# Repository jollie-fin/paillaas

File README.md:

# paillaas

## Context

I had decided in 2021 to leave my job and start a business, Kaukolab, to develop tools for better remote learning :

I have fond memories of session of lab work during my studies. Unfortunately, they are hard to do with remote learning. The only offers I saw on the market during my research were either based on simulations, with lots of simplification compared to the real world, or based on a few video of real experiments, but with almost no user input. Part of the experience of lab work is to experiment, break things, discover what is true and not simply check what you know is true is true.

My idea was to have real physical experiments users could connect to through Internet

## Lego prototype

A fun demonstration, where a user could control a pendulum hidden under my bed through a web interface.

The stack was the following :

- A pendulum in LEGO was hanged under my bed
- An EV3 brick with a flywheel was running a micro python kernel was communicating through an SSH connection.
  Its main tasks were : - receiving commands : - shorten/lenghten the pendulum - change how the the flywheel was controlled - retrieving and transmitting measurements from sensors - angle to the vertical - executing a simple kernel to control the flywheel
- An RPI was :
  - connected through ssh to the EV3
  - running a nodejs server that would exchange with EV3 and with a puppeteer instance
  - running a puppeteer instance that would transmit through WebRTC telemetry to a peer user, transmit a videofeed, and receive commands for the EV3
  - running a Discord bot that allowed remote management from my phone
- A remote server was :
  - serving an HTML page to the puppeteer instance on the RPI
  - serving an HTML page to end-users.
    The page was : - establishing a WebRTC connection with the RPI - displaying the telemetry to the user - allowing the user to define their own data to display through a DSL

This made for a weird stack, but it was reliable enough for me to make real demo of the concept I had.

I'm sadden that I wasn't able to push this prototype beyond it's MVP status. I had big projects like a Michelson interferometer totally controlled through internet

Some files were unfortunately lost, so I don't have a good showcase of it

## PCB design

A few pcb were designed during this adventure. Since it was in the middle of component crisis, I had to change quite a few the design, depending on component availabilities.

In hindsight, just buying a Duet Board would have been the best, but prices at that time were prohibitive

### Ethernet2serial

This is a simple serial converter, based on an atmega and an ENC28J60

### Motherboard

This aimed at connecting a Compute Module 4 to stepper motor drivers.

### Motherboard ITX-form-factor

This aimed at connecting a Compute Module 4 to stepper motor drivers. It also provides HDMI, DSI and CSI connections.

It also means I had to take care of high speed routing, with controlled impedance and differential pairs

It uses ITX screw holes, the idea being of using ITX cases

### USB2stepper

This was the final board. It is a 4 steppers board controlled by a RPI Pico, using TMC2208

A few interesting facts :

- TMC2208 were used at the limit of what they can handle
  - It means quite a bit of heat dissipation
  - Thermal vias were used to connect to the bottom side
  - A heatsink was bolted to the underside
  - To prevent short-circuit, no via (beside GND) could be used, forcing the design to be fully single layer under the heatsink
- The layer stackup was somewhat none conventional :
  - Top: signal
  - In1: GND
  - In2: GND/Power
  - Bottom: GND/Signal
  - The traces on the bottom layer were routed only over the ground plane part of In2

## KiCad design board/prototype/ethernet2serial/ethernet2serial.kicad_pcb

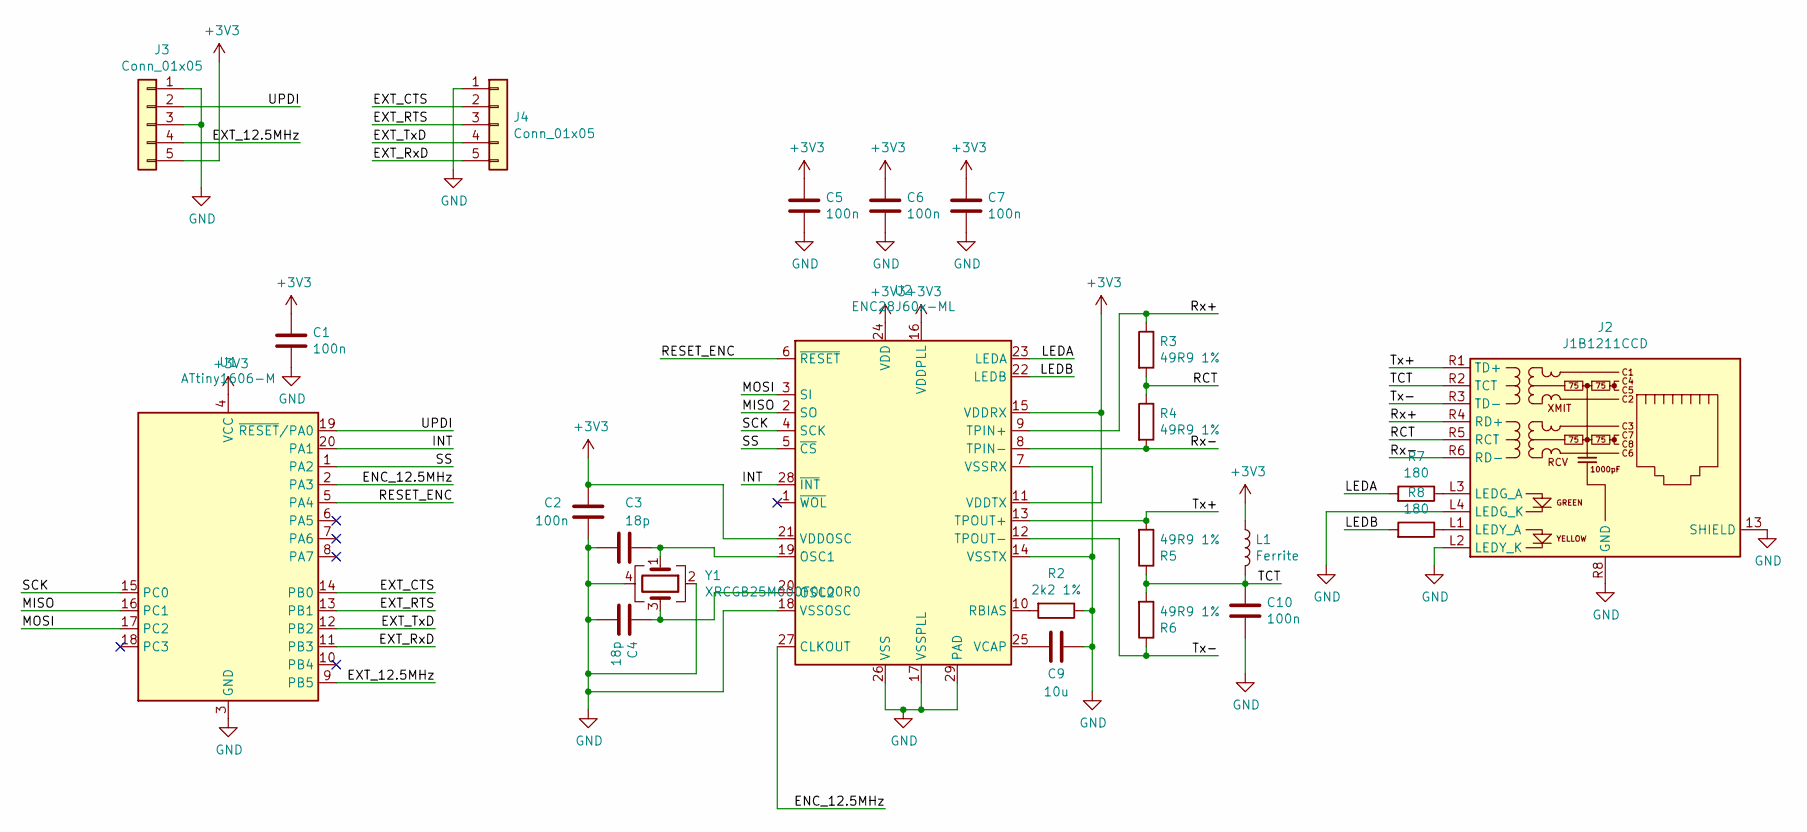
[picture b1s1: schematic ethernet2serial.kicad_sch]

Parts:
C1, C2, C5, C6, C7, C10: 100n; C_0402_1005Metric
C3, C4: 18p; C_0402_1005Metric
C9: 10u; C_0805_2012Metric
J2: J1B1211CCD; RJ45_Amphenol_RJMG1BD3B8K1ANR
J3, J4: Conn_01x05; PinHeader_1x05_P2.54mm_Vertical
L1: Ferrite; L_0402_1005Metric
R2: 2k2 1%; R_0402_1005Metric
R3, R4, R5, R6: 49R9 1%; R_0402_1005Metric
R7, R8: 180; R_0402_1005Metric
U1: ATtiny1606-M; VQFN-20-1EP_3x3mm_P0.4mm_EP1.7x1.7mm
U2: ENC28J60x-ML; QFN-28-1EP_6x6mm_P0.65mm_EP4.25x4.25mm
Y1: XRCGB25M000F0L00R0; Crystal_SMD_2016-4Pin_2.0x1.6mm

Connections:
+3V3: C1.1, C2.1, C5.1, C6.1, C7.1, J3.5, L1.1, U1.4 (VCC), U2.11 (VDDTX), U2.15 (VDDRX), U2.16 (VDDPLL), U2.21 (VDDOSC), U2.24 (VDD)
/ENC_12.5MHz: U1.2 (PA3), U2.27 (CLKOUT)
/EXT_12.5MHz: J3.4, U1.9 (PB5)
/EXT_CTS: J4.2, U1.14 (PB0)
/EXT_RTS: J4.3, U1.13 (PB1)
/EXT_RxD: J4.5, U1.11 (PB3)
/EXT_TxD: J4.4, U1.12 (PB2)
/INT: U1.20 (PA1), U2.28 (~INT)
/LEDA: R7.2, U2.23 (LEDA)
/LEDB: R8.2, U2.22 (LEDB)
/MISO: U1.16 (PC1), U2.2 (SO)
/MOSI: U1.17 (PC2), U2.3 (SI)
/RCT: J2.R5 (RCT), R3.2, R4.1
/RESET_ENC: U1.5 (PA4), U2.6 (~RESET)
/Rx+: J2.R4 (RD+), R3.1, U2.9 (TPIN+)
/Rx-: J2.R6 (RD-), R4.2, U2.8 (TPIN-)
/SCK: U1.15 (PC0), U2.4 (SCK)
/SS: U1.1 (PA2), U2.5 (~CS)
/TCT: C10.1, J2.R2 (TCT), L1.2, R5.1, R6.2
/Tx+: J2.R1 (TD+), R5.2, U2.13 (TPOUT+)
/Tx-: J2.R3 (TD-), R6.1, U2.12 (TPOUT-)
/UPDI: J3.2, U1.19 (~RESET/PA0)
GND: C1.2, C2.2, C3.1, C4.1, C5.2, C6.2, C7.2, C9.1, C10.2, J2.13 (SHIELD), J2.L2 (LEDY_K), J2.L4 (LEDG_K), J2.R8 (GND), J3.1, J3.3, J4.1, R2.1, U1.3 (GND), U1.21 (GND), U2.7 (VSSRX), U2.14 (VSSTX), U2.17 (VSSPLL), U2.18 (VSSOSC), U2.26 (VSS), U2.29 (PAD), Y1.2, Y1.4
unnamed: C3.2, U2.19 (OSC1), Y1.1
unnamed: C4.2, U2.20 (OSC2), Y1.3
unnamed: C9.2, U2.25 (VCAP)
unnamed: J2.L1 (LEDY_A), R8.1
unnamed: J2.L3 (LEDG_A), R7.1
unnamed: R2.2, U2.10 (RBIAS)

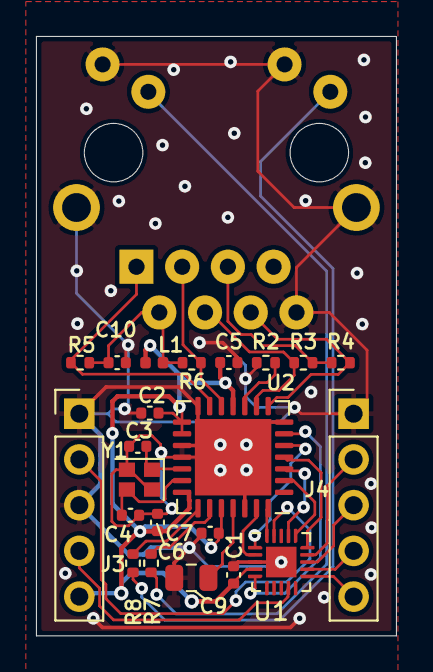
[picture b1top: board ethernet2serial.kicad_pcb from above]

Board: 2 copper layers, 20.0 x 33.3 mm, 23 parts (1 on the bottom side), 29 nets.

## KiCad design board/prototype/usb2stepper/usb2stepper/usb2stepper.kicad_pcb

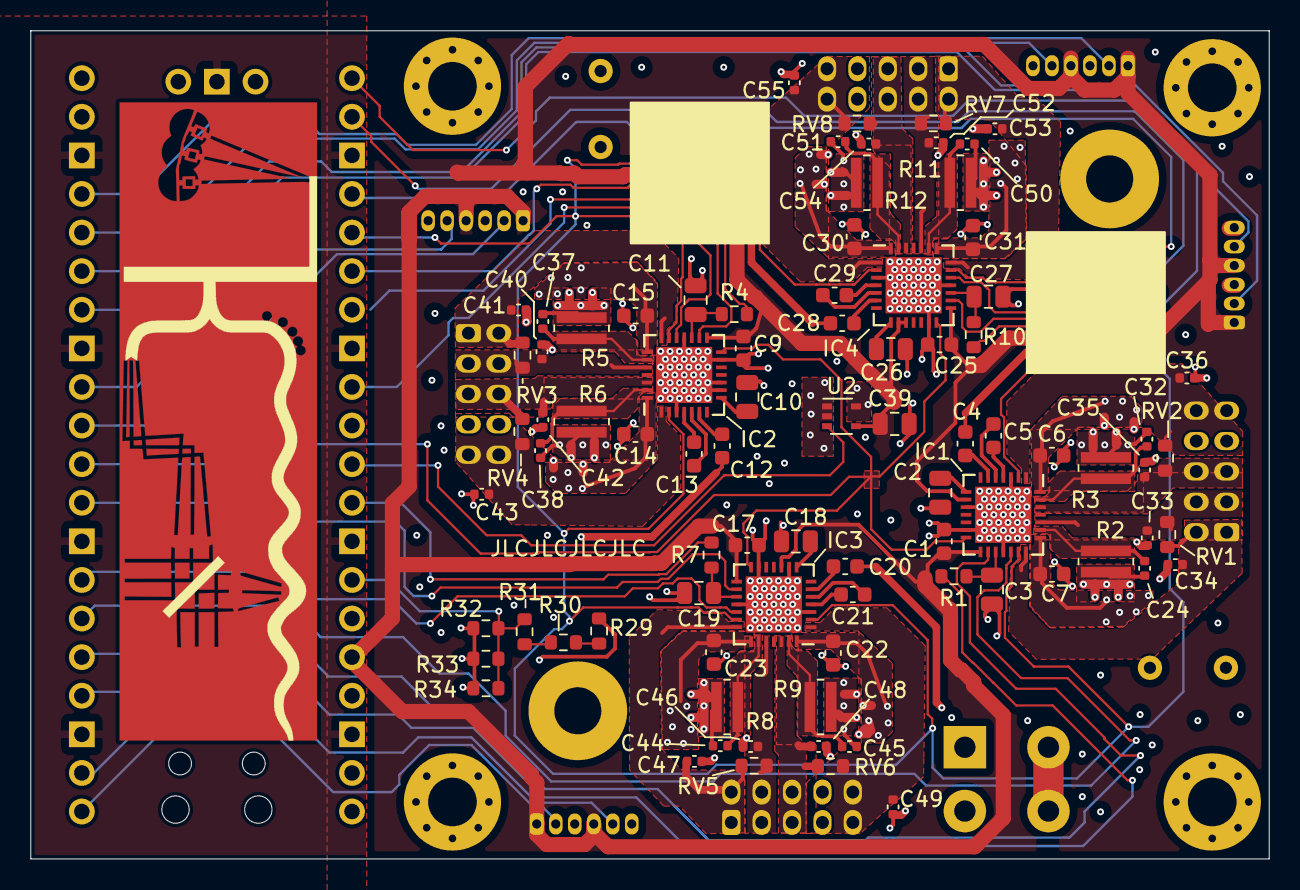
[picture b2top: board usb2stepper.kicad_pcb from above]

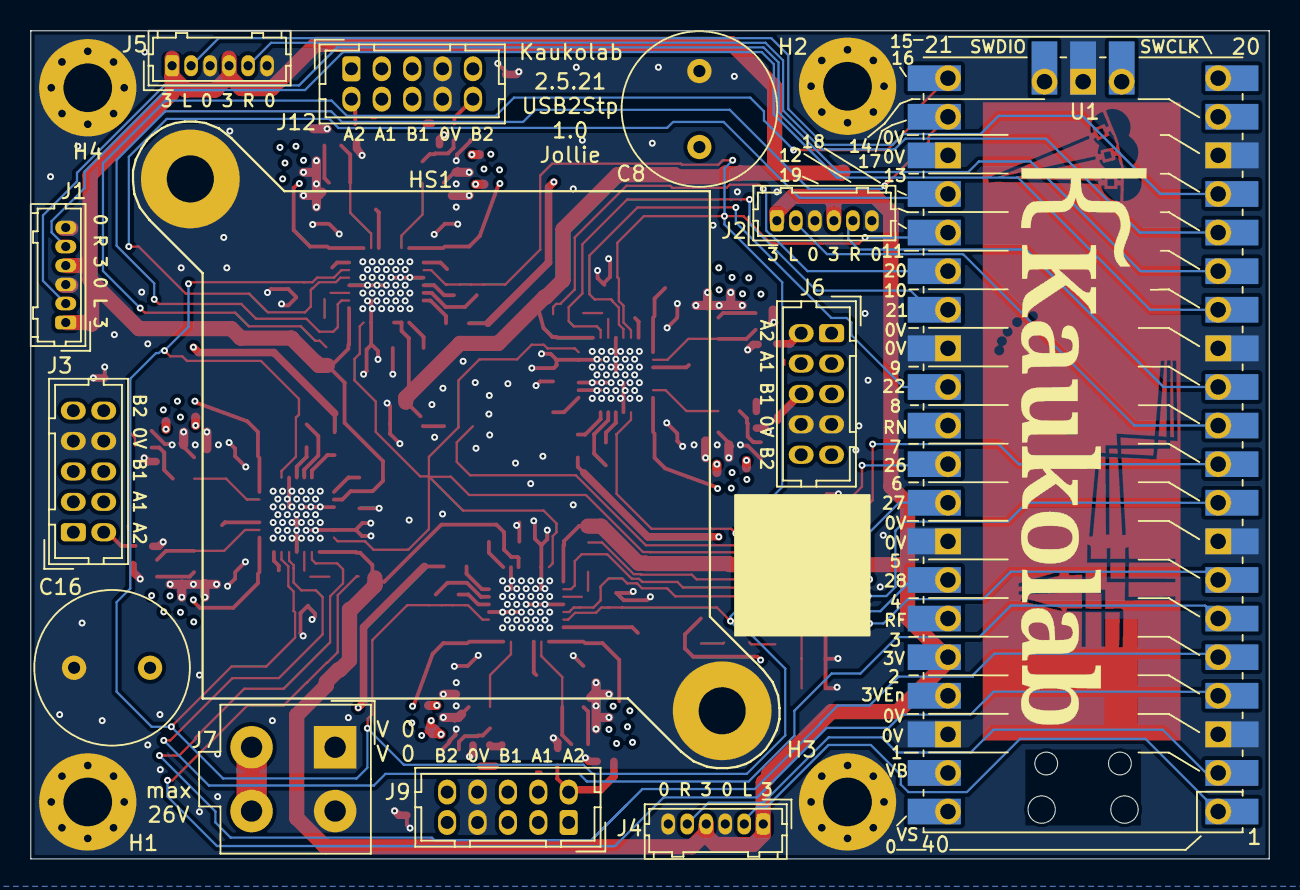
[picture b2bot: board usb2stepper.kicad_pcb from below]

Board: 4 copper layers, 81.5 x 54.5 mm, 103 parts (18 on the bottom side), 73 nets.

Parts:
C1, C4, C6, C7, C9, C12, C14, C15, C17, C20, C22, C23, C25, C28, C30, C31: 100n; C_0603_1608Metric
C2, C3, C10, C11, C18, C19, C26, C27, C39: 2u2 16V; C_0805_2012Metric
C5, C13, C21, C29: 22n; C_0603_1608Metric
C8, C16: 470uF; C_Radial_D10.0mm_H20.0mm_P5.00mm
C24, C32, C37, C38, C44, C45, C50, C51: 100nF NF; C_0402_1005Metric
C33, C34, C35, C36, C40, C41, C42, C43, C46, C47, C48, C49, C52, C53, C54, C55: 470pF 100V NF; C_0402_1005Metric
H1, H2, H3, H4: 3mm; MountingHole_3.2mm_M3_Pad_Via
HS1: 30x30mm; PCB_Heatsink_30x30mm_2xFixation3mm
IC1, IC2, IC3, IC4: TMC2209-LA; QFN-28-1EP_5x5mm_Pitch0.5mm_EP3.7x3.7
J1, J2, J4, J5: Conn_01x06; Hirose_DF13-06P-1.25DSA_1x06_P1.25mm_Vertical
J3, J6, J9, J12: Conn_02x05_Odd_Even; Hirose_DF11-10DP-2DSA_2x05_P2.00mm_Vertical
J7: Minifit_jr_2x2; Molex_MiniFit-JR-5556-04A_2x02x4.20mm_Straight
Logo1: Logo; Logo Silkscreen 40x9
Logo2: Logo; Logo All Layers 42x13
R1, R4, R7, R10, R29, R30, R31, R32, R33, R34: 10k; R_0603_1608Metric
R2, R3, R5, R6, R8, R9, R11, R12: 0.1; R_1206_Wide
RV1, RV2, RV3, RV4, RV5, RV6, RV7, RV8: Varistor; R_0603_1608Metric
U1: Pico; RPi_Pico_SMD_TH
U2: MCP9700AT-ELT; SOT-353_SC-70-5

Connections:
+3V3: C1.1, C9.1, C17.1, C25.1, C39.1, IC1.9 (MS1), IC1.15 (VCC_IO), IC2.15 (VCC_IO), IC3.10 (MS2), IC3.15 (VCC_IO), IC4.9 (MS1), IC4.10 (MS2), IC4.15 (VCC_IO), J1.1, J1.4, J2.1, J2.4, J4.1, J4.4, J5.1, J5.4, U1.36 (3V3), U2.4 (Vdd)
/24V_measure: R31.1, R32.2, R33.2, R34.2, U1.34 (GPIO28_ADC2)
/DIR0: IC1.19 (DIR), U1.6 (GPIO4)
/DIR1: IC2.19 (DIR), U1.29 (GPIO22)
/DIR2: IC3.19 (DIR), U1.7 (GPIO5)
/DIR3: IC4.19 (DIR), U1.24 (GPIO18)
/DISABLE_MOT: IC1.2 (ENN), IC1.20 (STDBY), IC2.2 (ENN), IC2.20 (STDBY), IC3.2 (ENN), IC3.20 (STDBY), IC4.2 (ENN), IC4.20 (STDBY), U1.25 (GPIO19)
/REFL0: J1.2, U1.15 (GPIO11)
/REFL1: J2.2, U1.11 (GPIO8)
/REFL2: J4.2, U1.1 (GPIO0)
/REFL3: J5.2, U1.17 (GPIO13)
/REFR0: J1.5, U1.14 (GPIO10)
/REFR1: J2.5, U1.12 (GPIO9)
/REFR2: J4.5, U1.2 (GPIO1)
/REFR3: J5.5, U1.16 (GPIO12)
/STEP0: IC1.16 (STEP), U1.5 (GPIO3)
/STEP1: IC2.16 (STEP), U1.27 (GPIO21)
/STEP2: IC3.16 (STEP), U1.9 (GPIO6)
/STEP3: IC4.16 (STEP), U1.22 (GPIO17)
/Sheet608F6F9E/BRA: C24.1, IC1.23 (BRA), R2.2
/Sheet608F6F9E/BRB: C32.1, IC1.27 (BRB), R3.2
/Sheet608F6F9E/OA1: C33.1, IC1.24 (OA1), J3.3, J3.4, RV1.1
/Sheet608F6F9E/OA2: C34.1, IC1.21 (OA2), J3.1, J3.2, RV1.2
/Sheet608F6F9E/OB1: C35.1, IC1.26 (OB1), J3.5, J3.6, RV2.1
/Sheet608F6F9E/OB2: C36.1, IC1.1 (OB2), J3.9, J3.10, RV2.2
/Sheet608F6F9E/Vref: C3.1, IC1.17 (VREF), R1.1
/TEMP: U1.31 (GPIO26_ADC0), U2.3 (Vout)
/UART: IC1.14 (PDN_UART), IC2.14 (PDN_UART), IC3.14 (PDN_UART), IC4.14 (PDN_UART), U1.10 (GPIO7)
/VREF_PWM0: R1.2, U1.4 (GPIO2)
/VREF_PWM1: R4.2, U1.26 (GPIO20)
/VREF_PWM2: R7.2, U1.32 (GPIO27_ADC1)
/VREF_PWM3: R10.2, U1.21 (GPIO16)
/sheet6092AD70/BRA: C50.1, IC4.23 (BRA), R11.2
/sheet6092AD70/BRB: C51.1, IC4.27 (BRB), R12.2
/sheet6092AD70/OA1: C52.1, IC4.24 (OA1), J12.3, J12.4, RV7.1
/sheet6092AD70/OA2: C53.1, IC4.21 (OA2), J12.1, J12.2, RV7.2
/sheet6092AD70/OB1: C54.1, IC4.26 (OB1), J12.5, J12.6, RV8.1
/sheet6092AD70/OB2: C55.1, IC4.1 (OB2), J12.9, J12.10, RV8.2
/sheet6092AD70/Vref: C27.1, IC4.17 (VREF), R10.1
/sheet609275BA/BRA: C37.1, IC2.23 (BRA), R5.2
/sheet609275BA/BRB: C38.1, IC2.27 (BRB), R6.2
/sheet609275BA/OA1: C40.1, IC2.24 (OA1), J6.3, J6.4, RV3.1
/sheet609275BA/OA2: C41.1, IC2.21 (OA2), J6.1, J6.2, RV3.2
/sheet609275BA/OB1: C42.1, IC2.26 (OB1), J6.5, J6.6, RV4.1
/sheet609275BA/OB2: C43.1, IC2.1 (OB2), J6.9, J6.10, RV4.2
/sheet609275BA/Vref: C11.1, IC2.17 (VREF), R4.1
/sheet60929021/BRA: C44.1, IC3.23 (BRA), R8.2
/sheet60929021/BRB: C45.1, IC3.27 (BRB), R9.2
/sheet60929021/OA1: C46.1, IC3.24 (OA1), J9.3, J9.4, RV5.1
/sheet60929021/OA2: C47.1, IC3.21 (OA2), J9.1, J9.2, RV5.2
/sheet60929021/OB1: C48.1, IC3.26 (OB1), J9.5, J9.6, RV6.1
/sheet60929021/OB2: C49.1, IC3.1 (OB2), J9.9, J9.10, RV6.2
/sheet60929021/Vref: C19.1, IC3.17 (VREF), R7.1
GND: C1.2, C2.2, C3.2, C6.2, C7.2, C8.2, C9.2, C10.2, C11.2, C14.2, C15.2, C16.2, C17.2, C18.2, C19.2, C22.2, C23.2, C24.2, C25.2, C26.2, C27.2, C30.2, C31.2, C32.2, C33.2, C34.2, C35.2, C36.2, C37.2, C38.2, C39.2, C40.2, C41.2, C42.2, C43.2, C44.2, C45.2, C46.2, C47.2, C48.2, C49.2, C50.2, C51.2, C52.2, C53.2, C54.2, C55.2, H1.1, H2.1, H3.1, H4.1, HS1.2, HS1.3, IC1.3 (GND), IC1.10 (MS2), IC1.13 (CLK), IC1.18 (GND), IC1.29 (GND), IC2.3 (GND), IC2.9 (MS1), IC2.10 (MS2), IC2.13 (CLK), IC2.18 (GND), IC2.29 (GND), IC3.3 (GND), IC3.9 (MS1), IC3.13 (CLK), IC3.18 (GND), IC3.29 (GND), IC4.3 (GND), IC4.13 (CLK), IC4.18 (GND), IC4.29 (GND), J1.3, J1.6, J2.3, J2.6, J3.7, J3.8, J4.3, J4.6, J5.3, J5.6, J6.7, J6.8, J7.1, J7.2, J9.7, J9.8, J12.7, J12.8, R2.1, R3.1, R5.1, R6.1, R8.1, R9.1, R11.1, R12.1, R32.1, R33.1, R34.1, U1.3 (GND), U1.8 (GND), U1.13 (GND), U1.18 (GND), U1.23 (GND), U1.28 (GND), U1.33 (AGND), U1.38 (GND), U1.42 (GND), U2.1 (NC), U2.2 (GND), U2.5 (NC)
unnamed: C2.1, IC1.8 (5VOUT)
unnamed: C4.2, IC1.6 (VCP)
unnamed: C5.1, IC1.5 (CPI)
unnamed: C5.2, IC1.4 (CPO)
unnamed: C10.1, IC2.8 (5VOUT)
unnamed: C12.2, IC2.6 (VCP)
unnamed: C13.1, IC2.5 (CPI)
unnamed: C13.2, IC2.4 (CPO)
unnamed: C18.1, IC3.8 (5VOUT)
unnamed: C20.2, IC3.6 (VCP)
unnamed: C21.1, IC3.5 (CPI)
unnamed: C21.2, IC3.4 (CPO)
unnamed: C26.1, IC4.8 (5VOUT)
unnamed: C28.2, IC4.6 (VCP)
unnamed: C29.1, IC4.5 (CPI)
unnamed: C29.2, IC4.4 (CPO)
unnamed: R29.1, R30.2
unnamed: R30.1, R31.2
Vdrive: C4.1, C6.1, C7.1, C8.1, C12.1, C14.1, C15.1, C16.1, C20.1, C22.1, C23.1, C28.1, C30.1, C31.1, IC1.22 (VS), IC1.28 (VS), IC2.22 (VS), IC2.28 (VS), IC3.22 (VS), IC3.28 (VS), IC4.22 (VS), IC4.28 (VS), J7.3, J7.4, R29.2

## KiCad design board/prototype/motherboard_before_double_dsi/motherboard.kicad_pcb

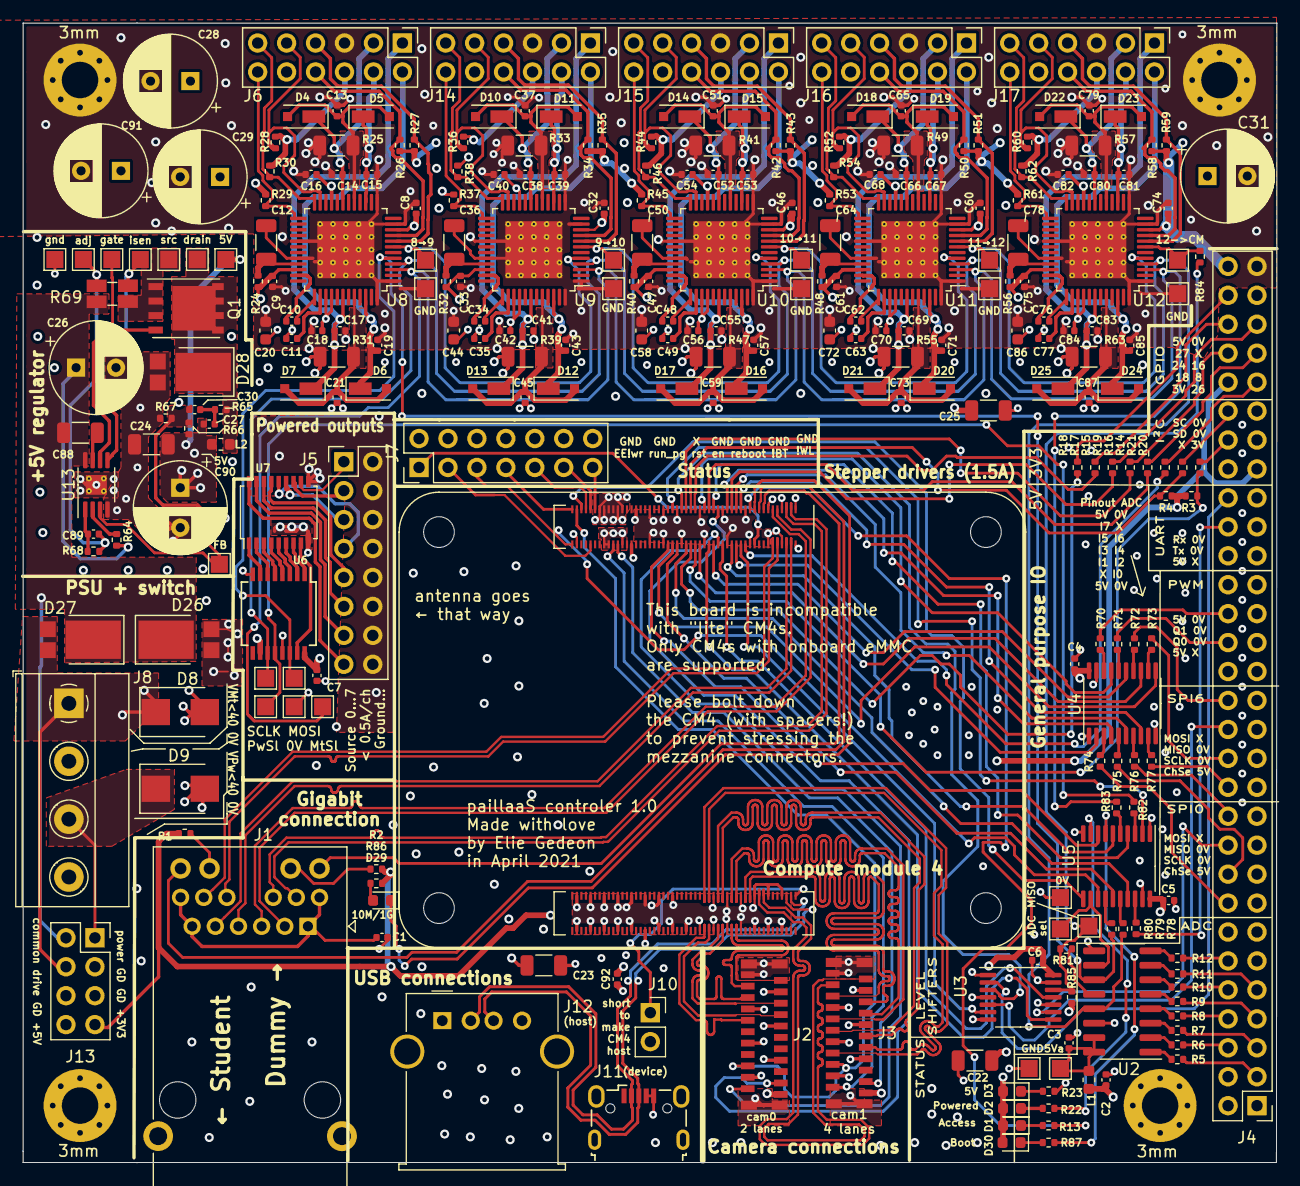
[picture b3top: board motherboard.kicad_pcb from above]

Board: 4 copper layers, 110.0 x 100.0 mm, 273 parts (0 on the bottom side), 249 nets.

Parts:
C1, C2, C3, C4, C5, C6, C7, C8, C11, C13, C16, C18, C21, C30, C32, C35, C37, C40, C42, C45, C46, C49, C51, C54, C56, C59, C60, C63, C65, C68, C70, C73, C74, C77, C79, C82, C84, C87: 100n; C_0402_1005Metric
C9, C33, C47, C61, C75: 470n; C_0402_1005Metric
C10, C34, C48, C62, C76: 22n; C_0402_1005Metric
C12, C22, C23, C24, C25, C36, C50, C64, C78: 10u; C_1206_3216Metric
C14, C15, C17, C19, C38, C39, C41, C43, C52, C53, C55, C57, C66, C67, C69, C71, C80, C81, C83, C85: 470p; C_0402_1005Metric
C20, C44, C58, C72, C86: 1u; C_0603_1608Metric
C26: 33u; CP_Radial_D8.0mm_P3.50mm
C27: 3n3; C_0402_1005Metric
C28, C29, C31, C90, C91: 100u; CP_Radial_D8.0mm_P3.50mm
C88: 4u7; C_1206_3216Metric
C89: 1n; C_0402_1005Metric
C92: 10n; C_0402_1005Metric
D1: GREEN; LED_0603_1608Metric
D2: RED; LED_0603_1608Metric
D3: BLUE; LED_0603_1608Metric
D4, D5, D6, D7, D10, D11, D12, D13, D14, D15, D16, D17, D18, D19, D20, D21, D22, D23, D24, D25: MSS1P5; DO-219AD
D8, D9: SMBJ43A; D_SMB
D26, D27, D28: SDT8A60VP5; D_PowerDI-5
D29: LED; LED_0603_1608Metric
D30: YELLOW; LED_0603_1608Metric
H1, H2, H3, H4: MountingHole_Pad; MountingHole_3.2mm_M3_Pad_Via
J1: JK0654218Z; RJ45_Pulse_JK0654219NL_Horizontal
J2, J3: Conn_01x22_MountingPin; 5019512230_1x22-1MP_P0.5mm_Vertical
J4: Conn_02x30_Odd_Even; PinHeader_2x30_P2.54mm_Vertical
J5: Conn_02x08_Odd_Even; PinHeader_2x08_P2.54mm_Vertical
J6, J14, J15, J16, J17: pin_header_02x06; PinHeader_2x06_P2.54mm_Vertical
J7: Conn_02x07_Odd_Even; PinHeader_2x07_P2.54mm_Vertical
J8: Conn_01x04; TerminalBlock_Phoenix_MKDS-1,5-4-5.08_1x04_P5.08mm_Horizont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
J10: Conn_01x02; PinSocket_1x02_P2.54mm_Vertical
J11: USB_B; USB_Micro-B_Wuerth_629105150521
J12: USB_A; USB_A_Molex_67643_Horizontal
J13: Conn_02x04_Odd_Even; PinSocket_2x04_P2.54mm_Vertical
L1, L2: 15uH; L_0603_1608Metric
Q1: Si7465DP; PowerPAK_SO-8_Single
R1, R2, R86: 470; R_0402_1005Metric
R3, R4: 1K8; R_0402_1005Metric
R5, R6, R7, R8, R9, R10, R11, R12, R14, R15, R16, R17, R18, R19, R20, R21, R70, R71, R72, R73, R74, R75, R76, R77, R78: 100; R_0402_1005Metric
R13, R22, R23, R26, R27, R28, R29, R30, R34, R35, R36, R37, R38, R42, R43, R44, R45, R46, R50, R51, R52, R53, R54, R58, R59, R60, R61, R62, R87: 4K7; R_0402_1005Metric
R24, R32, R40, R48, R56: 10; R_0402_1005Metric
R25, R31, R33, R39, R41, R47, R49, R55, R57, R63: 0.13; R_1206_3216Metric
R64: 90k9; R_0402_1005Metric
R65: 66k5; R_0402_1005Metric
R66, R85: 10k; R_0402_1005Metric
R67: 3k4; R_0402_1005Metric
R68: 2k1; R_0402_1005Metric
R69: L4T12FR010FER(0.01); R_Shunt_Ohmite_4LT12
R79, R80, R81, R82, R83, R84: 30; R_0402_1005Metric
TP1, TP2, TP3, TP4, TP5, TP6, TP7, TP8, TP9, TP10, TP11, TP12, TP13, TP14, TP15, TP16, TP17, TP18, TP19, TP20, TP21, TP23, TP24, TP25, TP26, TP27, TP28, TP29: TestPoint; TestPoint_Pad_1.5x1.5mm
U1: Compute_Module_4_Functional; Raspberry-Pi-4-Compute-Module
U2: MCP3008; SOIC-16_3.9x9.9mm_P1.27mm
U3: 74LVC125; TSSOP-14_4.4x5mm_P0.65mm
U4, U5: 74HCT244; TSSOP-20_4.4x6.5mm_P0.65mm
U6: 74HC595; SSOP-16_5.3x6.2mm_P0.65mm
U7: TBD62783A; SSOP-18_4.4x6.5mm_P0.65mm
U8, U9, U10, U11, U12: TMC5130A-TA; TQFP-48-1EP_7x7mm_P0.5mm_EP5x5mm_ThermalVias
U13: LM25085MY; MSOP-8-1EP_3x3mm_P0.65mm_EP1.73x1.85mm_ThermalVias

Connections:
+3V3: C6.1, C92.1, J2.22, J3.22, J4.45, J4.52, J13.7, R1.2, R2.2, R3.1, R4.1, R86.2, U1.78, U1.84, U1.86, U3.14
+5V: C2.1, C4.1, C5.1, C7.1, C8.1, C9.1, C22.1, C23.1, C24.1, C25.1, C27.1, C32.1, C33.1, C46.1, C47.1, C60.1, C61.1, C74.1, C75.1, C90.1, D1.2, D2.2, D3.2, D30.2, J4.2, J4.14, J4.15, J4.23, J4.32, J4.38, J4.40, J4.60, J6.6, J12.1, J13.8, J14.6, J15.6, J16.6, J17.6, L1.2, L2.1, R24.1, R26.1, R27.1, R28.1, R29.1, R30.1, R32.1, R34.1, R35.1, R36.1, R37.1, R38.1, R40.1, R42.1, R43.1, R44.1, R45.1, R46.1, R48.1, R50.1, R51.1, R52.1, R53.1, R54.1, R56.1, R58.1, R59.1, R60.1, R61.1, R62.1, R66.1, R85.1, TP17.1, U1.77, U1.79, U1.81, U1.83, U1.85, U1.87, U4.20, U5.20, U6.10, U6.16, U8.10, U8.34, U9.10, U9.34, U10.10, U10.34, U11.10, U11.34, U12.10, U12.34
/CAM_GPIO: J2.17, J3.17, U1.97
/GPIO/ACT_LED: R13.2, U1.21
/GPIO/AIN0: R5.1, U2.1
/GPIO/AIN0P: J4.3, R5.2
/GPIO/AIN1: R6.1, U2.2
/GPIO/AIN1P: J4.6, R6.2
/GPIO/AIN2: R7.1, U2.3
/GPIO/AIN2P: J4.5, R7.2
/GPIO/AIN3: R8.1, U2.4
/GPIO/AIN3P: J4.8, R8.2
/GPIO/AIN4: R9.1, U2.5
/GPIO/AIN4P: J4.7, R9.2
/GPIO/AIN5: R10.1, U2.6
/GPIO/AIN5P: J4.10, R10.2
/GPIO/AIN6: R11.1, U2.7
/GPIO/AIN6P: J4.9, R11.2
/GPIO/AIN7: R12.1, U2.8
/GPIO/AIN7P: J4.12, R12.2
/GPIO/AIN_SELECT_3V: U1.58, U5.8
/GPIO/AIN_SELECT_5V: TP5.1, U2.10, U5.12
/GPIO/CS0: U1.41, U4.17
/GPIO/CS0P: J4.16, R74.2
/GPIO/CS6: U1.56, U4.11
/GPIO/CS6P: J4.24, R77.2
/GPIO/GPIO8: R16.1, U1.39
/GPIO/GPIO8P: J4.53, R16.2
/GPIO/GPIO16: R15.1, U1.29
/GPIO/GPIO16P: J4.55, R15.2
/GPIO/GPIO18: R19.1, U1.49
/GPIO/GPIO18P: J4.54, R19.2
/GPIO/GPIO24: R17.1, U1.45
/GPIO/GPIO24P: J4.56, R17.2
/GPIO/GPIO26: R14.1, U1.24
/GPIO/GPIO26P: J4.51, R14.2
/GPIO/GPIO27: R18.1, U1.48
/GPIO/GPIO27P: J4.58, R18.2
/GPIO/MISO: R81.1, R84.2, R85.2, TP2.1, U3.12
/GPIO/MISO0: U1.40, U3.8
/GPIO/MISO0P: J4.20, U3.9
/GPIO/MISO4_3V: U1.34, U3.11
/GPIO/MISO6: U1.26, U3.6
/GPIO/MISO6P: J4.28, U3.5
/GPIO/MOSI: R80.2, TP4.1, U2.11, U6.14, U8.5
/GPIO/MOSI0: U1.44, U4.13
/GPIO/MOSI0P: J4.22, R76.2
/GPIO/MOSI4_3V: U1.30, U5.6
/GPIO/MOSI6: U1.27, U4.6
/GPIO/MOSI6P: J4.30, R72.2
/GPIO/MOTOR_SELECT: R83.2, TP7.1, U8.3, U9.3, U10.3, U11.3, U12.3
/GPIO/MOTOR_SELECT_3V: U1.54, U5.15
/GPIO/POWERED: R22.2, U5.9
/GPIO/POWER_SELECT: R82.2, TP21.1, U6.12
/GPIO/POWER_SELECT_3V: U1.50, U5.17
/GPIO/PWM0: U1.31, U4.4
/GPIO/PWM0P: J4.34, R71.2
/GPIO/PWM1: U1.28, U4.2
/GPIO/PWM1P: J4.36, R70.2
/GPIO/RxD0: U1.51, U3.3
/GPIO/RxD0P: J4.44, U3.2
/GPIO/SCL6: R4.2, R21.1, U1.47
/GPIO/SCL6P: J4.50, R21.2
/GPIO/SCLK: R79.2, TP3.1, U2.13, U6.11, U8.4, U9.4, U10.4, U11.4, U12.4
/GPIO/SCLK0: U1.38, U4.15
/GPIO/SCLK0P: J4.18, R75.2
/GPIO/SCLK4_3V: U1.37, U5.4
/GPIO/SCLK6: U1.25, U4.8
/GPIO/SCLK6P: J4.26, R73.2
/GPIO/SDA6: R3.2, R20.1, U1.46
/GPIO/SDA6P: J4.48, R20.2
/GPIO/TxD0: U1.55, U5.2
/GPIO/TxD0P: J4.42, R78.2
/GPIO/nEXTRST: J7.5, U1.100, U5.13
/GPIO/nEXTRST_pow: R87.2, U5.7
/SCL0: J3.20, U1.80
/SCL1: J2.20, U1.35
/SDA0: J3.21, U1.82
/SDA1: J2.21, U1.36
/camera/CAM0C+: J2.9, U1.142
/camera/CAM0C-: J2.8, U1.140
/camera/CAM0D0+: J2.3, U1.130
/camera/CAM0D0-: J2.2, U1.128
/camera/CAM0D1+: J2.6, U1.136
/camera/CAM0D1-: J2.5, U1.134
/camera/CAM1C+: J3.9, U1.129
/camera/CAM1C-: J3.8, U1.127
/camera/CAM1D0+: J3.3, U1.117
/camera/CAM1D0-: J3.2, U1.115
/camera/CAM1D1+: J3.6, U1.123
/camera/CAM1D1-: J3.5, U1.121
/camera/CAM1D2+: J3.12, U1.135
/camera/CAM1D2-: J3.11, U1.133
/camera/CAM1D3+: J3.15, U1.141
/camera/CAM1D3-: J3.14, U1.139
/cm4/BT_disable: J7.11, U1.91
/cm4/EEPROMprotect: J7.1, U1.20
/cm4/LED_Pwr: U1.95, U5.11
/cm4/USB+: J11.3, J12.3, U1.105
/cm4/USB-: J11.2, J12.2, U1.103
/cm4/WL_disable: J7.13, U1.89
/cm4/global_en: J7.7, U1.99
/cm4/rpireboot: J7.9, U1.93
/cm4/run_pg: J7.3, U1.92
/ethernet/ETH_0+: J1.11, U1.12
/ethernet/ETH_0-: J1.10, U1.10
/ethernet/ETH_1+: J1.4, U1.4
/ethernet/ETH_1-: J1.5, U1.6
/ethernet/ETH_2+: J1.3, U1.11
/ethernet/ETH_2-: J1.2, U1.9
/ethernet/ETH_3+: J1.8, U1.3
/ethernet/ETH_3-: J1.9, U1.5
/ethernet/ETH_LED_green: J1.13, U1.15
/ethernet/ETH_LED_yellow: J1.16, U1.17
/power/ADJ: C89.2, R68.2, U13.1
/power/ADJb: C89.1, R68.1, R69.2, TP12.1
/power/FB: C30.2, R66.2, R67.1, TP19.1, U13.3
/power/ISEN: R69.3, TP13.1, U13.5
/power/RT: R64.1, U13.2
/power/VCC: C88.2, U13.7
/power/drain: D28.1, L2.2, Q1.5, R65.2, TP16.1
/power/gate: Q1.4, TP14.1, U13.6
/power/source: Q1.1, Q1.2, Q1.3, R69.4, TP15.1
/powerIO/LIMITL0: J6.7, R27.2, U8.8
/powerIO/LIMITL1: J14.7, R35.2, U9.8
/powerIO/LIMITL2: J17.7, R59.2, U12.8
/powerIO/LIMITL3: J16.7, R51.2, U11.8
/powerIO/LIMITL4: J15.7, R43.2, U10.8
/powerIO/LIMITR0: J6.8, R26.2, U8.9
/powerIO/LIMITR1: J14.8, R34.2, U9.9
/powerIO/LIMITR2: J17.8, R58.2, U12.9
/powerIO/LIMITR3: J16.8, R50.2, U11.9
/powerIO/LIMITR4: J15.8, R42.2, U10.9
/powerIO/OUT0: U6.15, U7.8
/powerIO/OUT1: U6.1, U7.7
/powerIO/OUT2: U6.2, U7.6
/powerIO/OUT3: U6.3, U7.5
/powerIO/OUT4: U6.4, U7.4
/powerIO/OUT5: U6.5, U7.3
/powerIO/OUT6: U6.6, U7.2
/powerIO/OUT7: U6.7, U7.1
/powerIO/SRC0: J5.15, U7.18
/powerIO/SRC1: J5.13, U7.17
/powerIO/SRC2: J5.11, U7.16
/powerIO/SRC3: J5.9, U7.15
/powerIO/SRC4: J5.7, U7.14
/powerIO/SRC5: J5.5, U7.13
/powerIO/SRC6: J5.3, U7.12
/powerIO/SRC7: J5.1, U7.11
/powerIO/motorU8/BRA: C21.1, D6.2, D7.2, R31.1, U8.44
/powerIO/motorU8/BRB: C13.1, D4.2, D5.2, R25.1, U8.17
/powerIO/motorU8/ENCA: J6.12, R29.2, U8.25
/powerIO/motorU8/ENCB: J6.11, R30.2, U8.24
/powerIO/motorU8/ENCN: J6.9, R28.2, U8.23
/powerIO/motorU8/FILTERED_5V: C12.2, R24.2, U8.33
/powerIO/motorU8/MISO: TP8.1, U8.7, U9.5
/powerIO/motorU8/MOT_A1: C19.1, D6.1, J6.2, U8.46
/powerIO/motorU8/MOT_A2: C17.1, D7.1, J6.1, U8.42
/powerIO/motorU8/MOT_B1: C15.1, D5.1, J6.4, U8.15
/powerIO/motorU8/MOT_B2: C14.1, D4.1, J6.3, U8.19
/powerIO/motorU9/BRA: C45.1, D12.2, D13.2, R39.1, U9.44
/powerIO/motorU9/BRB: C37.1, D10.2, D11.2, R33.1, U9.17
/powerIO/motorU9/ENCA: J14.12, R37.2, U9.25
/powerIO/motorU9/ENCB: J14.11, R38.2, U9.24
/powerIO/motorU9/ENCN: J14.9, R36.2, U9.23
/powerIO/motorU9/FILTERED_5V: C36.2, R32.2, U9.33
/powerIO/motorU9/MISO: TP10.1, U9.7, U10.5
/powerIO/motorU9/MOT_A1: C43.1, D12.1, J14.2, U9.46
/powerIO/motorU9/MOT_A2: C41.1, D13.1, J14.1, U9.42
/powerIO/motorU9/MOT_B1: C39.1, D11.1, J14.4, U9.15
/powerIO/motorU9/MOT_B2: C38.1, D10.1, J14.3, U9.19
/powerIO/motorU10/BRA: C59.1, D16.2, D17.2, R47.1, U10.44
/powerIO/motorU10/BRB: C51.1, D14.2, D15.2, R41.1, U10.17
/powerIO/motorU10/ENCA: J15.12, R45.2, U10.25
/powerIO/motorU10/ENCB: J15.11, R46.2, U10.24
/powerIO/motorU10/ENCN: J15.9, R44.2, U10.23
/powerIO/motorU10/FILTERED_5V: C50.2, R40.2, U10.33
/powerIO/motorU10/MISO: TP23.1, U10.7, U11.5
/powerIO/motorU10/MOT_A1: C57.1, D16.1, J15.2, U10.46
/powerIO/motorU10/MOT_A2: C55.1, D17.1, J15.1, U10.42
/powerIO/motorU10/MOT_B1: C53.1, D15.1, J15.4, U10.15
/powerIO/motorU10/MOT_B2: C52.1, D14.1, J15.3, U10.19
/powerIO/motorU11/BRA: C73.1, D20.2, D21.2, R55.1, U11.44
/powerIO/motorU11/BRB: C65.1, D18.2, D19.2, R49.1, U11.17
/powerIO/motorU11/ENCA: J16.12, R53.2, U11.25
/powerIO/motorU11/ENCB: J16.11, R54.2, U11.24
/powerIO/motorU11/ENCN: J16.9, R52.2, U11.23
/powerIO/motorU11/FILTERED_5V: C64.2, R48.2, U11.33
/powerIO/motorU11/MISO: TP25.1, U11.7, U12.5
/powerIO/motorU11/MOT_A1: C71.1, D20.1, J16.2, U11.46
/powerIO/motorU11/MOT_A2: C69.1, D21.1, J16.1, U11.42
/powerIO/motorU11/MOT_B1: C67.1, D19.1, J16.4, U11.15
/powerIO/motorU11/MOT_B2: C66.1, D18.1, J16.3, U11.19
/powerIO/motorU12/BRA: C87.1, D24.2, D25.2, R63.1, U12.44
/powerIO/motorU12/BRB: C79.1, D22.2, D23.2, R57.1, U12.17
/powerIO/motorU12/ENCA: J17.12, R61.2, U12.25
/powerIO/motorU12/ENCB: J17.11, R62.2, U12.24
/powerIO/motorU12/ENCN: J17.9, R60.2, U12.23
/powerIO/motorU12/FILTERED_5V: C78.2, R56.2, U12.33
/powerIO/motorU12/MISO: R84.1, TP27.1, U12.7
/powerIO/motorU12/MOT_A1: C85.1, D24.1, J17.2, U12.46
/powerIO/motorU12/MOT_A2: C83.1, D25.1, J17.1, U12.42
/powerIO/motorU12/MOT_B1: C81.1, D23.1, J17.4, U12.15
/powerIO/motorU12/MOT_B2: C80.1, D22.1, J17.3, U12.19
GND: C1.2, C2.2, C3.2, C4.2, C5.2, C6.2, C7.2, C8.2, C9.2, C12.1, C13.2, C14.2, C15.2, C16.2, C17.2, C18.2, C19.2, C20.2, C21.2, C22.2, C23.2, C24.2, C25.2, C26.2, C28.2, C29.2, C31.2, C32.2, C33.2, C36.1, C37.2, C38.2, C39.2, C40.2, C41.2, C42.2, C43.2, C44.2, C45.2, C46.2, C47.2, C50.1, C51.2, C52.2, C53.2, C54.2, C55.2, C56.2, C57.2, C58.2, C59.2, C60.2, C61.2, C64.1, C65.2, C66.2, C67.2, C68.2, C69.2, C70.2, C71.2, C72.2, C73.2, C74.2, C75.2, C78.1, C79.2, C80.2, C81.2, C82.2, C83.2, C84.2, C85.2, C86.2, C87.2, C90.2, C91.2, C92.2, D8.2, D9.2, D28.2, H1.1, H2.1, H3.1, H4.1, J1.SH, J2.1, J2.4, J2.7, J2.10, J2.13, J2.16, J2.19, J2.MP, J3.1, J3.4, J3.7, J3.10, J3.13, J3.16, J3.19, J3.MP, J4.1, J4.13, J4.17, J4.19, J4.25, J4.27, J4.33, J4.35, J4.37, J4.41, J4.43, J4.47, J4.49, J4.59, J5.2, J5.4, J5.6, J5.8, J5.10, J5.12, J5.14, J5.16, J6.5, J7.2, J7.4, J7.8, J7.10, J7.12, J7.14, J8.2, J8.4, J10.2, J11.4, J11.5, J12.4, J12.5, J13.3, J13.5, J13.6, J14.5, J15.5, J16.5, J17.5, R23.2, R25.2, R31.2, R33.2, R39.2, R41.2, R47.2, R49.2, R55.2, R57.2, R63.2, R67.2, TP6.1, TP9.1, TP11.1, TP18.1, TP20.1, TP24.1, TP26.1, TP28.1, TP29.1, U1.1, U1.2, U1.7, U1.8, U1.13, U1.14, U1.22, U1.23, U1.32, U1.33, U1.42, U1.43, U1.52, U1.53, U1.59, U1.60, U1.65, U1.66, U1.71, U1.74, U1.98, U1.107, U1.108, U1.113, U1.114, U1.119, U1.120, U1.125, U1.126, U1.131, U1.132, U1.137, U1.138, U1.144, U1.150, U1.155, U1.156, U1.161, U1.162, U1.167, U1.168, U1.173, U1.174, U1.179, U1.180, U1.185, U1.186, U1.191, U1.192, U1.197, U1.198, U2.9, U2.14, U3.1, U3.4, U3.7, U3.10, U3.13, U4.1, U4.10, U4.19, U5.1, U5.10, U5.19, U6.8, U6.13, U7.10, U8.1, U8.11, U8.13, U8.29, U8.32, U8.48, U8.49, U9.1, U9.11, U9.13, U9.29, U9.32, U9.48, U9.49, U10.1, U10.11, U10.13, U10.29, U10.32, U10.48, U10.49, U11.1, U11.11, U11.13, U11.29, U11.32, U11.48, U11.49, U12.1, U12.11, U12.13, U12.29, U12.32, U12.48, U12.49, U13.4, U13.9
unnamed: C1.1, J1.1, J1.6, J1.7, J1.12
unnamed: C3.1, L1.1, TP1.1, U2.15, U2.16
unnamed: C10.1, U8.37
unnamed: C10.2, U8.35
unnamed: C11.1, U8.38
unnamed: C27.2, C30.1, R65.1
unnamed: C34.1, U9.37
unnamed: C34.2, U9.35
unnamed: C35.1, U9.38
unnamed: C48.1, U10.37
unnamed: C48.2, U10.35
unnamed: C49.1, U10.38
unnamed: C62.1, U11.37
unnamed: C62.2, U11.35
unnamed: C63.1, U11.38
unnamed: C76.1, U12.37
unnamed: C76.2, U12.35
unnamed: C77.1, U12.38
unnamed: D1.1, R13.1
unnamed: D2.1, R22.1
unnamed: D3.1, R23.1
unnamed: D29.1, U1.19
unnamed: D29.2, R86.1
unnamed: D30.1, R87.1
unnamed: J1.14, R2.1
unnamed: J1.15, R1.1
unnamed: J10.1, U1.101
unnamed: R70.1, U4.18
unnamed: R71.1, U4.16
unnamed: R72.1, U4.14
unnamed: R73.1, U4.12
unnamed: R74.1, U4.3
unnamed: R75.1, U4.5
unnamed: R76.1, U4.7
unnamed: R77.1, U4.9
unnamed: R78.1, U5.18
unnamed: R79.1, U5.16
unnamed: R80.1, U5.14
unnamed: R81.2, U2.12
unnamed: R82.1, U5.3
unnamed: R83.1, U5.5
VPP: C26.1, C88.1, D26.1, D27.1, J13.2, R64.2, R69.1, U13.8
VS: D9.1, D26.2, J8.3, J13.1, U7.9
Vdrive: C11.2, C16.1, C18.1, C20.1, C28.1, C29.1, C31.1, C35.2, C40.1, C42.1, C44.1, C49.2, C54.1, C56.1, C58.1, C63.2, C68.1, C70.1, C72.1, C77.2, C82.1, C84.1, C86.1, C91.1, D8.1, D27.2, J8.1, J13.4, U8.21, U8.39, U8.40, U9.21, U9.39, U9.40, U10.21, U10.39, U10.40, U11.21, U11.39, U11.40, U12.21, U12.39, U12.40
